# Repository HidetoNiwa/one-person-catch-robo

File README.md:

# one-person-catch-robo

[#１人キャチロボ]() のリポジトリ

## CAD

* 全体.iam：ロボット全体設計（フィールド込み）
* ロボット.iam：ロボット設計

そのほか、構造解析レポートとかもあります。

### 開発ソフトウェア

Autodesk Inventor Professional 2020

学生版ライセンスで使用可能

## KiCAD

* メインボード.pro：メインボードの設計

### 開発ソフトウェア

KiCAD 5.1.3

## 公式提出資料

## YOLO環境構築

### 環境

Jetson Nano

### 方法

https://www.nakasha.co.jp/future/ai/vol2_yolov3nvidia_jetson_nano.html

OpenCVのver.4系だとうまくコンパイル-できなかった

https://pickerlab.net/2018/08/06/darknet-eroor-nvcc/

### 学習用ファイルラベリング「labelimg」

参考；https://symfoware.blog.fc2.com/blog-entry-2420.html

PyQTのバージョン：5.14.1
デフォルトのインストール設定では、5.10.1になっているのを書き換える（pip配布の問題）

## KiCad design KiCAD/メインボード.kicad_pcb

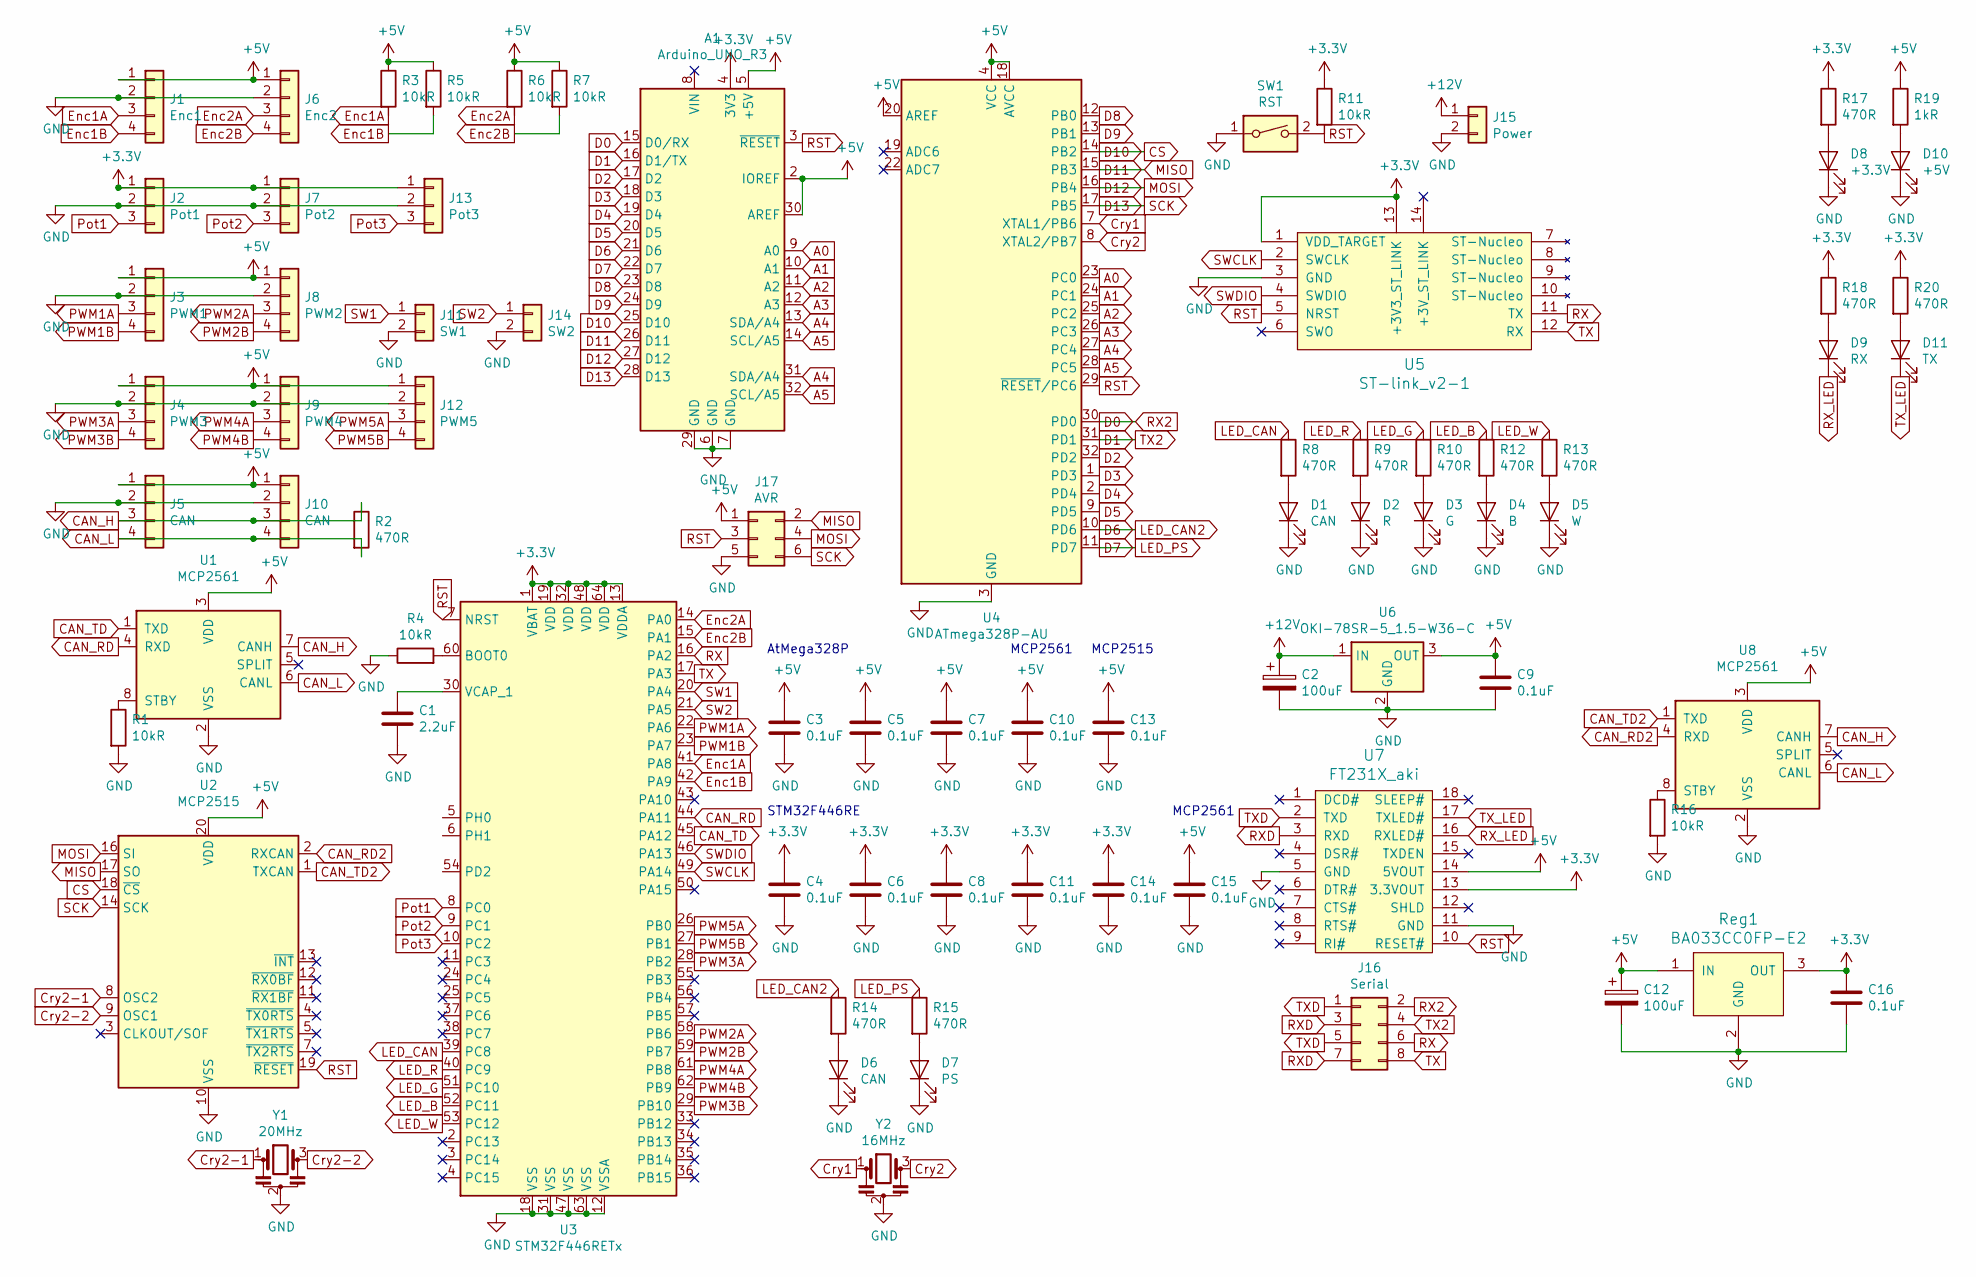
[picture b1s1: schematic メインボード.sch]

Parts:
A1: Arduino_UNO_R3
C1: 2.2uF; C_0603_1608Metric_Pad1.05x0.95mm_HandSolder
C2, C12: 100uF; CP_Elec_5x3
C3, C4, C5, C6, C7, C8, C9, C10, C11, C13, C14, C15, C16: 0.1uF; C_0603_1608Metric_Pad1.05x0.95mm_HandSolder
D1, D6: CAN; LED_0603_1608Metric_Pad1.05x0.95mm_HandSolder
D2: R; LED_0603_1608Metric_Pad1.05x0.95mm_HandSolder
D3: G; LED_0603_1608Metric_Pad1.05x0.95mm_HandSolder
D4: B; LED_0603_1608Metric_Pad1.05x0.95mm_HandSolder
D5: W; LED_0603_1608Metric_Pad1.05x0.95mm_HandSolder
D7: PS; LED_0603_1608Metric_Pad1.05x0.95mm_HandSolder
D8: +3.3V; LED_D3.0mm
D9: RX; LED_0603_1608Metric_Pad1.05x0.95mm_HandSolder
D10: +5V; LED_D3.0mm
D11: TX; LED_0603_1608Metric_Pad1.05x0.95mm_HandSolder
J1: Enc1; XA_4
J2: Pot1; XA_3
J3: PWM1; XA_4
J4: PWM3; XA_4
J5, J10: CAN; XA_4_Angled
J6: Enc2; XA_4
J7: Pot2; XA_3
J8: PWM2; XA_4
J9: PWM4; XA_4
J11: SW1; XA_2
J12: PWM5; XA_4
J13: Pot3; XA_3
J14: SW2; XA_2
J15: Power; VL_2
J16: Serial; PinHeader_2x04_P2.54mm_Vertical
J17: AVR; PinHeader_2x03_P2.54mm_Vertical
R1, R3, R4, R5, R6, R7, R11, R16: 10kR; R_0603_1608Metric_Pad1.05x0.95mm_HandSolder
R2, R8, R9, R10, R12, R13, R14, R15, R17, R18, R20: 470R; R_0603_1608Metric_Pad1.05x0.95mm_HandSolder
R19: 1kR; R_0603_1608Metric_Pad1.05x0.95mm_HandSolder
Reg1: BA033CC0FP-E2; TO-252-2
SW1: RST; SW_PUSH_6mm
U1, U8: MCP2561; SOIC-8_3.9x4.9mm_P1.27mm
U2: MCP2515; TSSOP-20_4.4x6.5mm_P0.65mm
U3: STM32F446RETx; LQFP-64_10x10mm_P0.5mm
U4: ATmega328P-AU; TQFP-32_7x7mm_P0.8mm
U5: ST-link_v2-1
U6: OKI-78SR-5_1.5-W36-C; Converter_DCDC_muRata_OKI-78SR_Vertical
U7: FT231X_aki
Y1: 20MHz; Resonator-3Pin_W6.0mm_H3.0mm
Y2: 16MHz; Resonator-3Pin_W6.0mm_H3.0mm

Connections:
+3V3: A1.4 (3V3), C4.1, C6.1, C8.1, C11.1, C14.1, C16.1, J2.1, J7.1, J13.1, R11.1, R17.1, R18.1, R20.1, Reg1.3 (OUT), U3.1 (VBAT), U3.13 (VDDA), U3.19 (VDD), U3.32 (VDD), U3.48 (VDD), U3.64 (VDD), U5.1 (VDD_TARGET), U5.13 (+3V3_ST_LINK), U7.13 (3.3VOUT)
+5V: A1.2 (IOREF), A1.5 (+5V), A1.30 (AREF), C3.1, C5.1, C7.1, C9.1, C10.1, C12.1, C13.1, C15.1, J1.1, J3.1, J4.1, J5.1, J6.1, J8.1, J9.1, J10.1, J12.1, J17.1, R3.1, R5.1, R6.1, R7.1, R19.1, Reg1.1 (IN), U1.3 (VDD), U2.20 (VDD), U4.4 (VCC), U4.6 (VCC), U4.18 (AVCC), U4.20 (AREF), U6.3 (OUT), U7.14 (5VOUT), U8.3 (VDD)
+12V: C2.1, J15.1, U6.1 (IN)
A0: A1.9 (A0), U4.23 (PC0)
A1: A1.10 (A1), U4.24 (PC1)
A2: A1.11 (A2), U4.25 (PC2)
A3: A1.12 (A3), U4.26 (PC3)
A4: A1.13 (SDA/A4), A1.31 (SDA/A4), U4.27 (PC4)
A5: A1.14 (SCL/A5), A1.32 (SCL/A5), U4.28 (PC5)
CAN_H: J5.3, J10.3, R2.1, U1.7 (CANH), U8.7 (CANH)
CAN_L: J5.4, J10.4, R2.2, U1.6 (CANL), U8.6 (CANL)
CAN_RD: U1.4 (RXD), U3.44 (PA11)
CAN_RD2: U2.2 (RXCAN), U8.4 (RXD)
CAN_TD: U1.1 (TXD), U3.45 (PA12)
CAN_TD2: U2.1 (TXCAN), U8.1 (TXD)
CS: A1.25 (D10), U2.18 (~CS), U4.14 (PB2)
Cry1: U4.7 (XTAL1/PB6), Y2.1
Cry2: U4.8 (XTAL2/PB7), Y2.3
Cry2-1: U2.8 (OSC2), Y1.1
Cry2-2: U2.9 (OSC1), Y1.3
D0: A1.15 (D0/RX), J16.2, U4.30 (PD0)
D1: A1.16 (D1/TX), J16.4, U4.31 (PD1)
D2: A1.17 (D2), U4.32 (PD2)
D3: A1.18 (D3), U4.1 (PD3)
D4: A1.19 (D4), U4.2 (PD4)
D5: A1.20 (D5), U4.9 (PD5)
D6: A1.21 (D6), R14.1, U4.10 (PD6)
D7: A1.22 (D7), R15.1, U4.11 (PD7)
D8: A1.23 (D8), U4.12 (PB0)
D9: A1.24 (D9), U4.13 (PB1)
D11: A1.26 (D11), J17.2, U2.17 (SO), U4.15 (PB3)
D12: A1.27 (D12), J17.4, U2.16 (SI), U4.16 (PB4)
D13: A1.28 (D13), J17.6, U2.14 (SCK), U4.17 (PB5)
Enc1A: J1.3, R3.2, U3.41 (PA8)
Enc1B: J1.4, R5.2, U3.42 (PA9)
Enc2A: J6.3, R6.2, U3.14 (PA0)
Enc2B: J6.4, R7.2, U3.15 (PA1)
GND: A1.6 (GND), A1.7 (GND), A1.29 (GND), C1.2, C2.2, C3.2, C4.2, C5.2, C6.2, C7.2, C8.2, C9.2, C10.2, C11.2, C12.2, C13.2, C14.2, C15.2, C16.2, D1.1 (K), D2.1 (K), D3.1 (K), D4.1 (K), D5.1 (K), D6.1 (K), D7.1 (K), D8.1 (K), D10.1 (K), J1.2, J2.2, J3.2, J4.2, J5.2, J6.2, J7.2, J8.2, J9.2, J10.2, J11.2, J12.2, J13.2, J14.2, J15.2, J17.5, R1.2, R4.1, R16.2, Reg1.2 (GND), SW1.1, U1.2 (VSS), U2.10 (VSS), U3.12 (VSSA), U3.18 (VSS), U3.31 (VSS), U3.47 (VSS), U3.63 (VSS), U4.3 (GND), U4.5 (GND), U4.21 (GND), U5.3 (GND), U6.2 (GND), U7.5 (GND), U7.11 (GND), U8.2 (VSS), Y1.2, Y2.2
LED_B: R12.1, U3.52 (PC11)
LED_CAN: R8.1, U3.39 (PC8)
LED_G: R10.1, U3.51 (PC10)
LED_R: R9.1, U3.40 (PC9)
LED_W: R13.1, U3.53 (PC12)
unnamed: C1.1, U3.30 (VCAP_1)
unnamed: D1.2 (A), R8.2
unnamed: D2.2 (A), R9.2
unnamed: D3.2 (A), R10.2
unnamed: D4.2 (A), R12.2
unnamed: D5.2 (A), R13.2
unnamed: D6.2 (A), R14.2
unnamed: D7.2 (A), R15.2
unnamed: D8.2 (A), R17.2
unnamed: D9.2 (A), R18.2
unnamed: D10.2 (A), R19.2
unnamed: D11.2 (A), R20.2
unnamed: R1.1, U1.8 (STBY)
unnamed: R4.2, U3.60 (BOOT0)
unnamed: R16.1, U8.8 (STBY)
PWM1A: J3.3, U3.22 (PA6)
PWM1B: J3.4, U3.23 (PA7)
PWM2A: J8.3, U3.58 (PB6)
PWM2B: J8.4, U3.59 (PB7)
PWM3A: J4.3, U3.28 (PB2)
PWM3B: J4.4, U3.29 (PB10)
PWM4A: J9.3, U3.61 (PB8)
PWM4B: J9.4, U3.62 (PB9)
PWM5A: J12.3, U3.26 (PB0)
PWM5B: J12.4, U3.27 (PB1)
Pot1: J2.3, U3.8 (PC0)
Pot2: J7.3, U3.9 (PC1)
Pot3: J13.3, U3.10 (PC2)
RST: A1.3 (~RESET), J17.3, R11.2, SW1.2, U2.19 (~RESET), U3.7 (NRST), U4.29 (~RESET~/PC6), U5.5 (NRST), U7.10 (RESET#)
RX: J16.6, U3.16 (PA2), U5.11 (TX)
RXD: J16.3, J16.7, U7.3 (RXD)
RX_LED: D9.1 (K), U7.16 (RXLED#)
SW1: J11.1, U3.20 (PA4)
SW2: J14.1, U3.21 (PA5)
SWCLK: U3.49 (PA14), U5.2 (SWCLK)
SWDIO: U3.46 (PA13), U5.4 (SWDIO)
TX: J16.8, U3.17 (PA3), U5.12 (RX)
TXD: J16.1, J16.5, U7.2 (TXD)
TX_LED: D11.1 (K), U7.17 (TXLED#)

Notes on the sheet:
STM32F446RE
MCP2515
MCP2561
AtMega328P

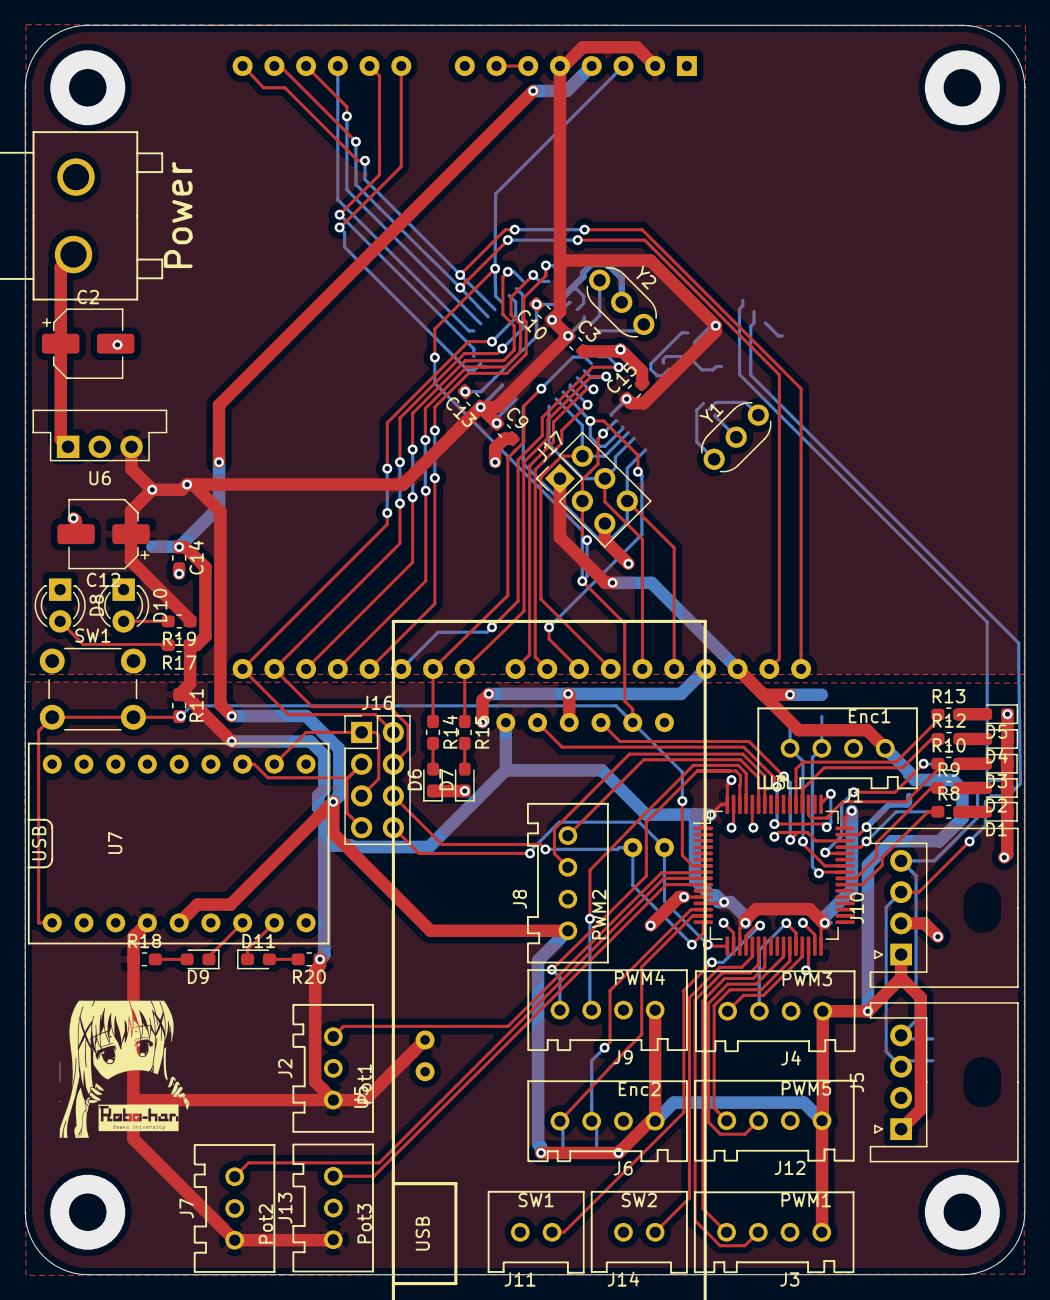
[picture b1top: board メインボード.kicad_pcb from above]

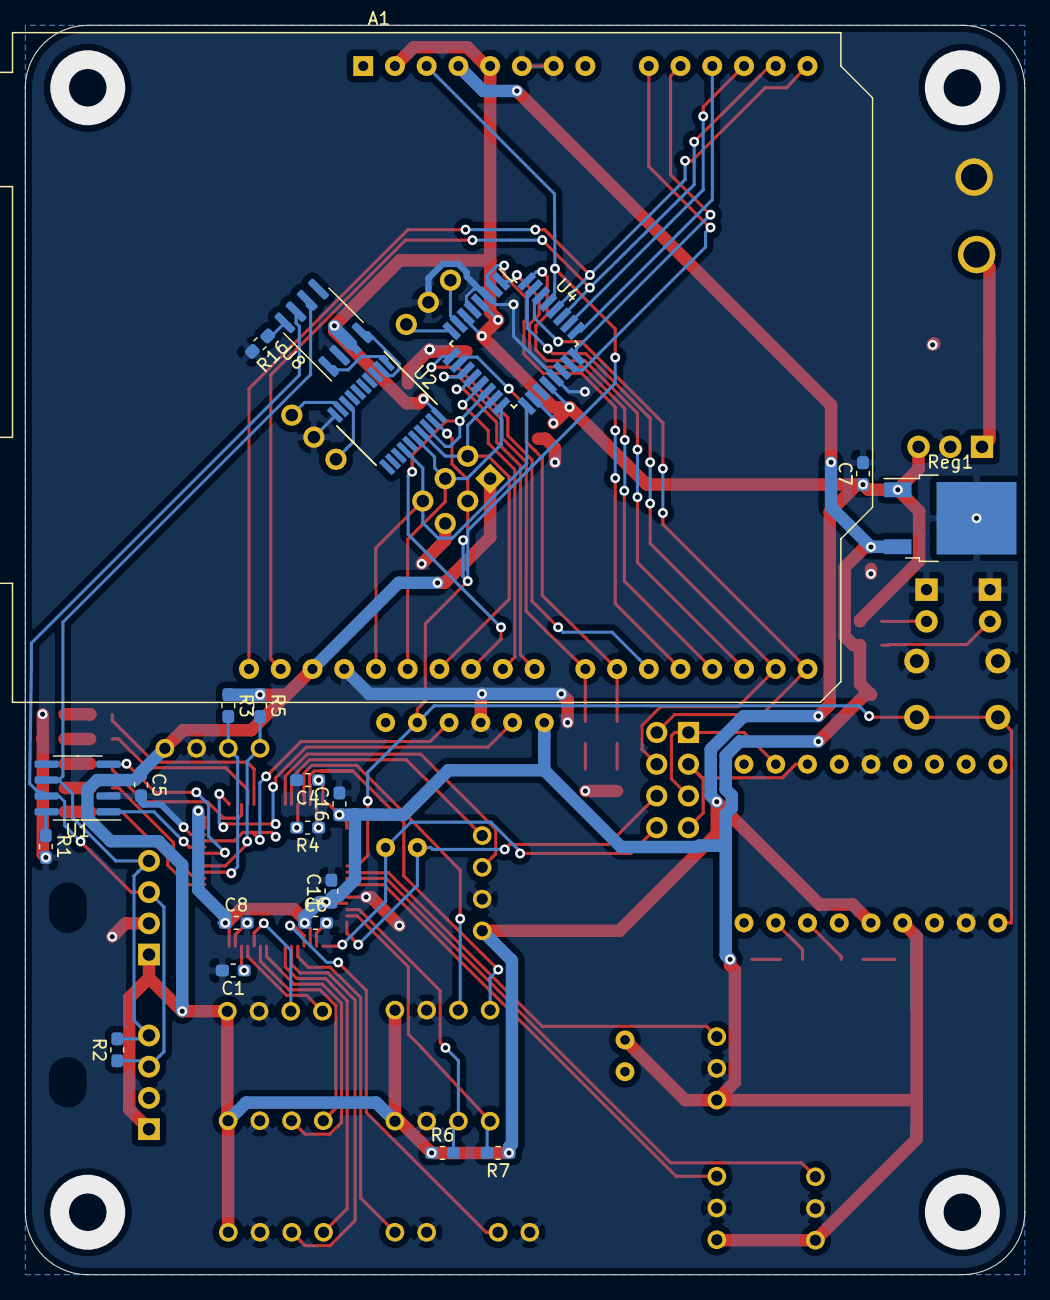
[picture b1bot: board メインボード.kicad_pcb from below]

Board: 2 copper layers, 80.0 x 100.0 mm, 77 parts (22 on the bottom side), 82 nets.

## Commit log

2020-08-30 Edit README
2020-08-31 作業に応じてMarkdown編集
2020-08-31 Add CAD & docs
2020-09-03 add label
2020-09-03 add YOLO setting
2020-09-16 edit movie data
2020-09-16 edit photo
2020-09-16 edit txt
2020-09-16 add ignore data
